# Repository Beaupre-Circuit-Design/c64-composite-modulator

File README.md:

# c64-rf-modulator-replacement
C64 Composite/S-Video RF Modulator Replacement

## Quick Links
* [Schematic](pdf/C64-Composite-Modulator.pdf)

* [Gerber Files](./gerbers)

* [PCB Renderings](./images)

* [Photos](./images)

# Introduction 
This is a remix of mbarszcz-pcb's version of a C64 RF Modulator replacement based on the schematics of similar designs like [Zero-X/OMS's Modified Commodore RF Modulator Design](images/zerox-oms-modulator_simple-schematic.png) and [JMP$FCE2's S-Video only design](images/jmp$fce2-schematic.png). This board can be used to replace a damaged or defective RF modulator in your C64, to improve the sharpness of your video output, or as a modern solution to replace the composite/luma/chroma output functionality of the original modulator on new motherboards such as the SixtyClone or Bwack’s KU-14194.

This design has a few goals that set it apart from the others:

1. It is a universal solution that fits and is electrically compatible with both the C64 and C64C without having to change components on the board or run jumper wires for power.

2. It is inexpensive to build with only a single, small PCB and SMD components that can be assemble by most rapid prototyping compagnies (everything included for JLCPCB but can be easilly adapted for any other service.)

3. It provides high quality S-Video (Y/C) output on the standard A/V output of the C64 while maintaining composite video output for compatibility.

4. It provides adjustable luma/chroma output levels to fine-tune the S-video signal. This allows for the best possible compatibility with a wide variety of different board revisions, VIC chips, aging components and monitors. Adjustable levels mean this board can also be used with s-video cables with or without an inline resistor to eliminate “checkerboarding” caused by too high of a chroma level.

# Compatibility
This RF modulator replacement is compatible with motherboard revisions 250407, 250425, 250466, and 250469, and both NTSC and PAL VIC-II chips. I have not tested it, but I believe it should also be compatible with Bwack's KU-14194 board as well since it uses the standard longboard RF modulator. It is not compatible, however, with the early revision 326298-01 boards with the 5 Pin AV Output. This revision uses a different modulator pin layout, and the video signals are not combined in the modulator. They are instead processed with discrete components inside the VIC-II can.

# Gathering the components
Kicad files are available for you to view or modify as you see fit. Gerber and SMT positioning files are available that can be uploaded directly to JLCPCB to make and assemble your own boards. The Bill of Materials (BOM) can be found [here](C64-Composite-Modulator-Bom.xlsx) with example parts from LCSC and Digikey.

I strongly recommend building the entire board, if you choose to do so, there are a few components that can be omitted in different situations to decrease the cost at the expense of features and flexibility.

## Trimmers
The trim pots used to adjust the luma and chroma are the most expensive components in this project. I highly recommend using them, but if you choose, you may ommit the trimmer pots and install 150Ω resistors instead. This won't give you the precision adjustment of the trimmers, but it will be close enough for most configurations. You can experiment with different fixed value resistors between 100-1KΩ if you want to change fixed output levels.

## No Composite Video
I have not seen any improvement in S-video quality by omitting the composite video components, but if you really don’t want composite output, L1, R8, R9, C6 and V1 can be omitted from the build.

## No Audio Output
A1 can be omitted from the build if you do not want an audio output. Audio will still be available thru the standard A/V output of the C64.

## No Voltage Regulator
If you are only ever going to use the RF modulator replacement on a C64C 250469 short board, you don’t need the voltage regulator or the input/output capacitors since 5V is provided directly to the modulator on pin 1. This means you can omit C1, C2, C3, C4, U1 from the build and permanently jump JP3 pin 2 and 3.

# Building the board
If you wish to assemble the board yourself, i greatly recommend having a SMD Stainless Steel stencil made with your PCB order if you're going with hot air or oven reflow. First step is to start with soldering all the SMD components then the throught holes ones. Finish off by removing the flux residue with some cotton swabs or a brush and isopropyl alcohol.

# Installing the board
First, you need to remove the old RF modulator. This can be a bit tricky as the large metal can will suck the heat right out of the iron. I can’t help you much here, but I can only suggest you use a soldering iron with plenty of heat, use a wide tip, to take your time, and don't rip off any traces. The new board can then be installed one of two ways.

I do not recommend soldering it directly to the motherboard, it will make things much more difficult to remove if you want to upgrade to something else in the futur or come back to the stock modulator.

The PCB can be cut at the dotted lines if you plan to install it on a C64C 250469 short board to reduce footprint.

First solder all the pin headers on the underside, use the LB positions for the large boards and SB for the short boards. Then install the females headers on the motherboards. I personally prefer the rounded pins/receptacles headers but square work just fine too. Solder the female signal headers before the support (LB/SB) headers.

# Adjustments

## Configuring the mainboard
If you are using the longboard (Rev 250407, 250425, 240441, 250466), ground is provided by the support headers, so there is no need to change the G.PAL/I.PAL jumper on the motherboard.

## Jumper Settings
JP1 need to be set accordingly to your VIC-II version, use position 1-2 for NMOS (656x) and 2-3 for HMOS-II (856x).

JP2 control the use of the on-board voltage regulator. For long boards (250407, 250425, and 250466), use position 1-2 to enable the on-board regulator and for C64C short boards (250469) use position 2-3 to bypass it since the board already provide 5v. If you're not sure, check the voltage at pin 2 of JP2. If you get 5v, use position 2-3, else 1-2.

## Adjusting the Output Level
If you choose to include adjustable potentiometers in your build, a counter-clockwise adjustment on the luma (Y) and chroma (C) potentiometers will reduce the output level. A clockwise adjustment will increase the output level. My recommendation is to start with both adjustments fully counter-clockwise and increase as necessary. The levels can be set with a scope or simply “by eye” depending on the tools you have available.

An ideal chroma signal should be ~300mV peak-to-peak (mesured at TP3). The adjustment on the board should allow you to adjust it from approximately ~250mV - 1.7V. This range allows you to dial back the output for use with a standard S-video cable or to turn it up to compensate for the cables with the inline 330-1K resistor. Some monitors don't care if the signal is too hot, others will give you an ugly checkered pattern (especially LCDs). If you don't have an oscilloscope to measure the peak-to-peak voltage, start with the chroma pot fully counter-clockwise and increase it until the colors are sufficiently saturated. If you go too far, the image will begin to look “grainy” or have a checkerboard pattern.

Officially, an ideal luma signal should be 1V PP (including the sync pulse, mesured at TP6). Depending on the output of the VIC-II chip you are using, the adjustment on the board should allow you to adjust it from approximately ~575mV-1.5V PP. The original breadbins output a signal around 1.2V PP, while the later C64Cs were closer to an “in-spec” 1V PP. On some monitors though 1V PP can look too look dark (requiring you to turn up the contrast on your monitor). If using a scope, I would adjust it to approximately 1.1V PP. If adjusting by eye, start low and increase the level until the light blue text is reasonably legible against the dark blue background. If the border and text start to look “white” you have gone too far. Another good test on a CRT is white text on a black background. If the white text is blooming, you should back the signal off. The effect will be very similar to having the contrast set too high.

Composite video output remains at a fixed output level regardless of the Y and C adjustment pots.

# A note on use with LCD Monitors and Checkerboarding
If you are still getting checkerboarding even after adjusting the potentiometers, try populating CO1 with a 330pF Resistor (you can experiement with different values to see what works best with your setup). This combines with R3 to create an RC filter that seems to help eliminate this. There seems to be a degree of variablility regarding different A->D conversion cirtuitry used in different brands of LCD monitors and in devices like the RetroTink2X or OSSC that makes some displays more susceptable to checkerboarding. CRT monitors are not as susceptable to this behavior.

# Changelog
* Rev 20210528-2008
  * Prototype
* Rev 20210531-2143 (Not working)
  * Move B1/B2 silkscreen reference to the right location.
  * Rotate JP1/JP2 so all the headers are aligned to the same side (Forgot to update the silkscreen)
  * Switch to a BC847 transistor but forgot to update the footprint.
* Rev 20220130-1040
  * Corrected aligment of the support headers.
  * Corrected wrong pinout on Q1/Q2.
  * Remove the dual-sid option, not really useful.
  * Change A1 to a RCA Phono jack.
  * Remove B1/B2, use the trimmer pot pads instead if replacing them with a fixed resistor value.
  * Change the footprint of the LCD FIX capacitor for a throught-hole.
  * PCB Layout rework.
  * Fully assembled and tested on both C64 and C64C motherboards.

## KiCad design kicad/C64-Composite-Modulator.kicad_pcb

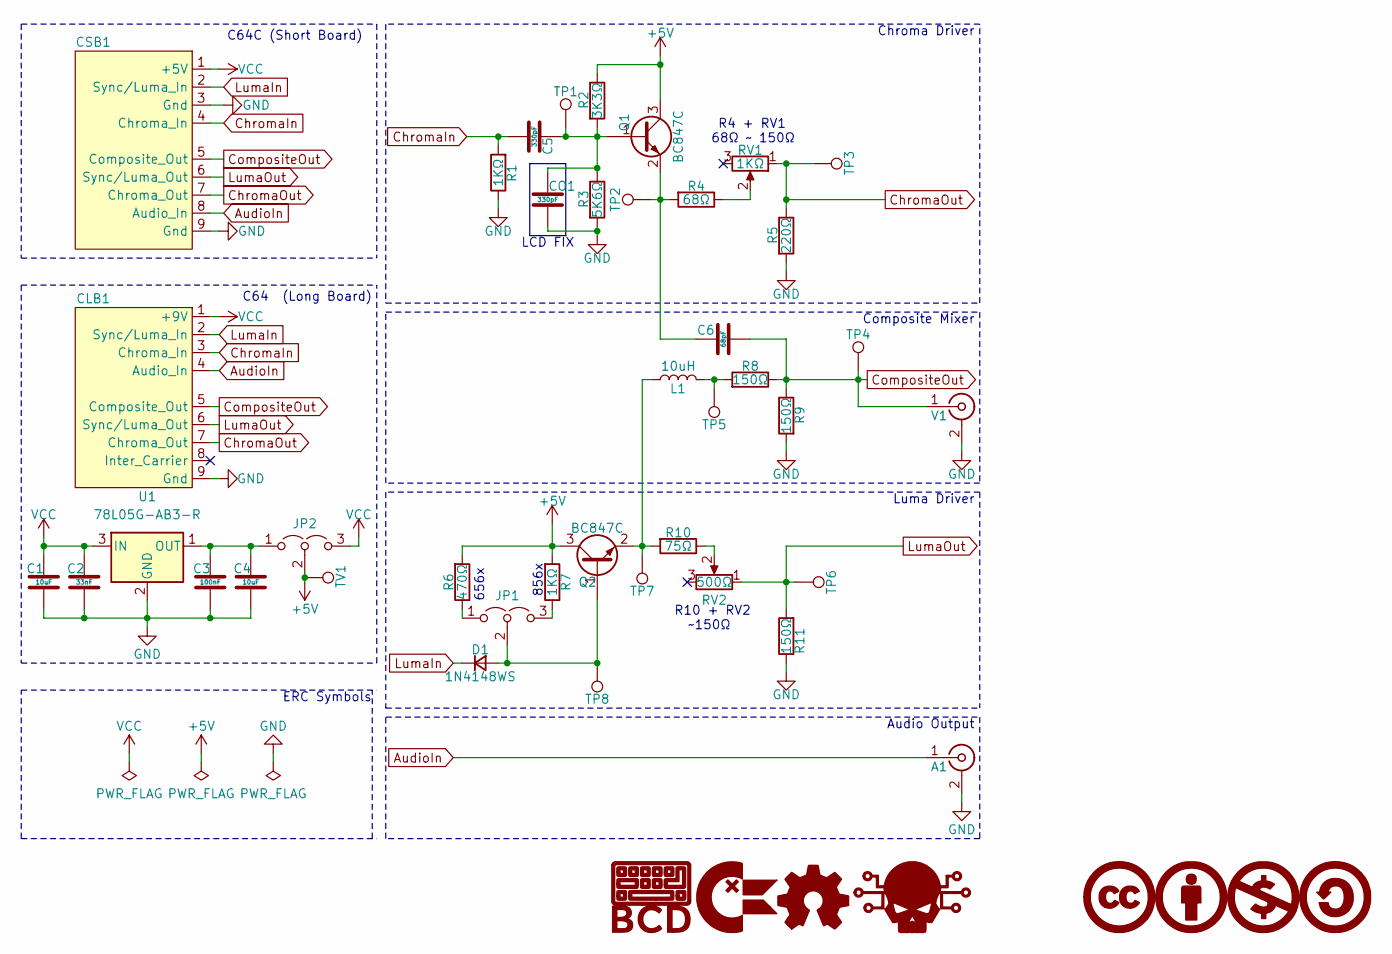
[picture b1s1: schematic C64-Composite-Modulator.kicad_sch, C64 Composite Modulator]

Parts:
A1: Conn_Coaxial; RCJ-013; Mfr.Part RCJ-014; Digikey CP-1403-ND
C1, C4: 10uF; C_1206_3216Metric; Mfr.Part CL31A106KBHNNNE; LCSC C13585
C2: 33nF; C_0805_2012Metric; Mfr.Part 0805B333K500NT; LCSC C1739
C3: 100nF; C_0805_2012Metric; Mfr.Part CL21B104KCFNNNE; LCSC C28233
C5: 330pF; C_0805_2012Metric; Mfr.Part CL21B331KBANNNC; LCSC C51207
C6: 68pF; C_0805_2012Metric; Mfr.Part CL21C680JBANNNC; LCSC C193697
CLB1: Modulator_Board_To_Long_Board; Modulator to Long-Board support; Mfr.Part C49257; Digikey 1212-1172-ND
CO1: 330pF; C_Disc_D4.7mm_W2.5mm_P5.00mm; Mfr.Part CK45-B3AD331KYVNA; LCSC C342340
CSB1: Modulator_Board_To_Short_Board; Modulator to Short-Board support; Mfr.Part C49257; Digikey 1212-1172-ND
D1: 1N4148WS; D_SOD-323F; Mfr.Part 1N4148WS; LCSC C2128
G1: BCD_Logo; BCD_Logo_5mm
G2: ChickenLips; ChickenLips_2.5mm
G3: OpenSource_Hardware; Open_Source_Hardware_2.5mm
G4: Skull; Skull_2.5mm
G5: CreativeCommons; CreativeCommons_2.5mm
G6: CreativeCommons_Attribution; CreativeCommons_Attribution_2.5mm
G7: CreativeCommons_NonCommercial; CreativeCommons_NonCommercial_2.5mm
G8: CreativeCommons_ShareAlike; CreativeCommons_ShareAlike_2.5mm
JP1, JP2: Jumper_3_Open; PinHeader_1x03_P2.54mm_Vertical; Mfr.Part C49257; LCSC C49257
L1: 10uH; L_0805_2012Metric; Mfr.Part SDFL2012S100KTF; LCSC C1046
Q1, Q2: BC847C; SOT-23; Mfr.Part BC847C,215; LCSC C8664
R1, R7: 1KΩ; R_0805_2012Metric; Mfr.Part 0805W8F1001T5E; LCSC C17513
R2: 3K3Ω; R_0805_2012Metric; Mfr.Part 0805W8F3301T5E; LCSC C26010
R3: 5K6Ω; R_0805_2012Metric; Mfr.Part 0805W8F5601T5E; LCSC C4382
R4: 68Ω; R_0805_2012Metric; Mfr.Part 0805W8F680JT5E; LCSC C17802
R5: 220Ω; R_0805_2012Metric; Mfr.Part 0805W8F2200T5E; LCSC C17557
R6: 470Ω; R_0805_2012Metric; Mfr.Part 0805W8F4700T5E; LCSC C17710
R8, R9, R11: 150Ω; R_0805_2012Metric; Mfr.Part 0805W8F1500T5E; LCSC C17471
R10: 75Ω; R_0805_2012Metric; Mfr.Part 0805W8F750JT5E; LCSC C17820
RV1: 1KΩ; Potentiometer_Bourns_3296W_Vertical; Mfr.Part 3296W-1-102; LCSC C118949
RV2: 500Ω; Potentiometer_Bourns_3296W_Vertical; Mfr.Part 3296W-1-500; LCSC C118908
TP1, TP2, TP3, TP4, TP5, TP6, TP7, TP8: TestPoint; TestPoint_THTPad_2.0x2.0mm_Drill1.0mm
TV1: TestPoint; TestPoint_THTPad_2.0x2.0mm_Drill1.0mm
U1: 78L05G-AB3-R; SOT-89-3; Mfr.Part 78L05G-AB3-R; LCSC C71136
V1: Conn_Coaxial; RCJ-014; Mfr.Part RCJ-014; Digikey CP-1403-ND

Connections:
+5V: JP2.2 (C), Q1.3 (C), Q2.3 (C), R2.1, R6.2, R7.2, TV1.1
AudioIn: A1.1 (In), CLB1.4 (Audio_In), CSB1.8 (Audio_In)
ChromaIn: C5.2, CLB1.3 (Chroma_In), CSB1.4 (Chroma_In), R1.2
ChromaOut: CLB1.7 (Chroma_Out), CSB1.7 (Chroma_Out), R5.1, RV1.1, TP3.1
CompositeOut: C6.1, CLB1.5 (Composite_Out), CSB1.5 (Composite_Out), R8.1, R9.1, TP4.1, V1.1 (In)
GND: A1.2 (Ext), C1.2, C2.2, C3.2, C4.2, CLB1.9 (Gnd), CO1.2, CSB1.3 (Gnd), CSB1.9 (Gnd), R1.1, R3.2, R5.2, R9.2, R11.1, U1.2 (GND), V1.2 (Ext)
LumaIn: CLB1.2 (Sync/Luma_In), CSB1.2 (Sync/Luma_In), D1.1 (K)
LumaOut: CLB1.6 (Sync/Luma_Out), CSB1.6 (Sync/Luma_Out), R11.2, RV2.1, TP6.1
unnamed: C3.1, C4.1, JP2.1 (A), U1.1 (OUT)
unnamed: C5.1, CO1.1, Q1.1 (B), R2.2, R3.1, TP1.1
unnamed: C6.2, Q1.2 (E), R4.2, TP2.1
unnamed: D1.2 (A), JP1.2 (C), Q2.1 (B), TP8.1
unnamed: JP1.1 (A), R6.1
unnamed: JP1.3 (B), R7.1
unnamed: L1.1, R8.2, TP5.1
unnamed: L1.2, Q2.2 (E), R10.2, TP7.1
unnamed: R4.1, RV1.2
unnamed: R10.1, RV2.2
VCC: C1.1, C2.1, CLB1.1 (+9V), CSB1.1 (+5V), JP2.3 (B), U1.3 (IN)

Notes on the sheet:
856x
R10 + RV2 ~150Ω
C64C (Short Board)
Luma Driver
Composite Mixer
C64 (Long Board)
ERC Symbols
Audio Output
R4 + RV1 68Ω ~ 150Ω
Chroma Driver
656x
LCD FIX

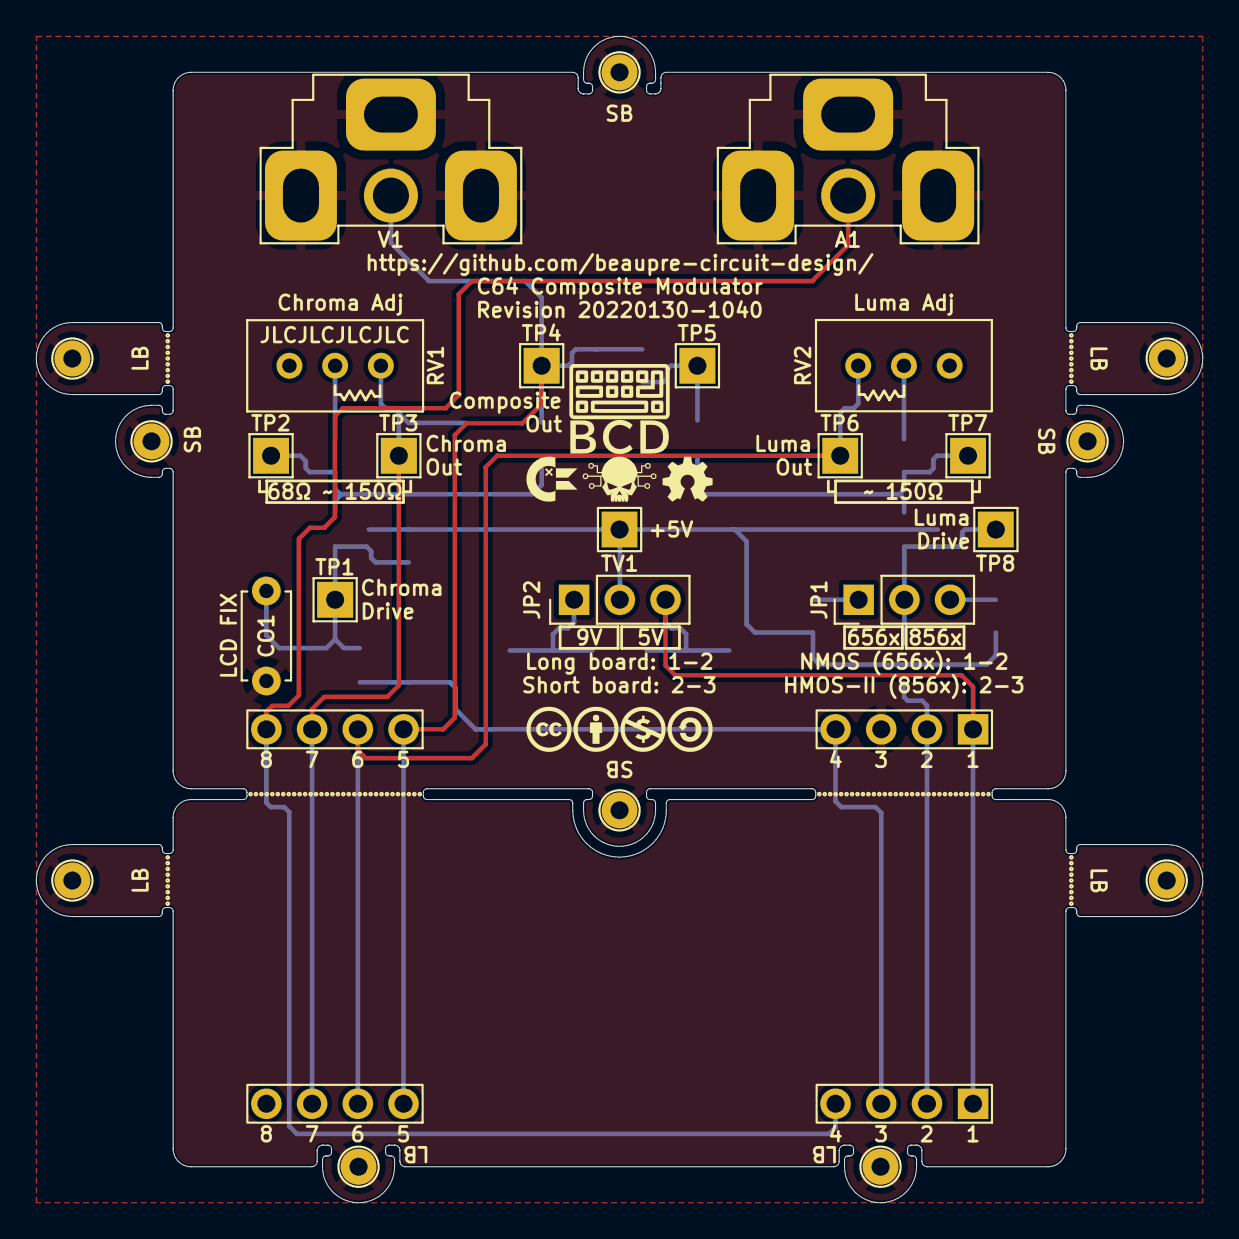
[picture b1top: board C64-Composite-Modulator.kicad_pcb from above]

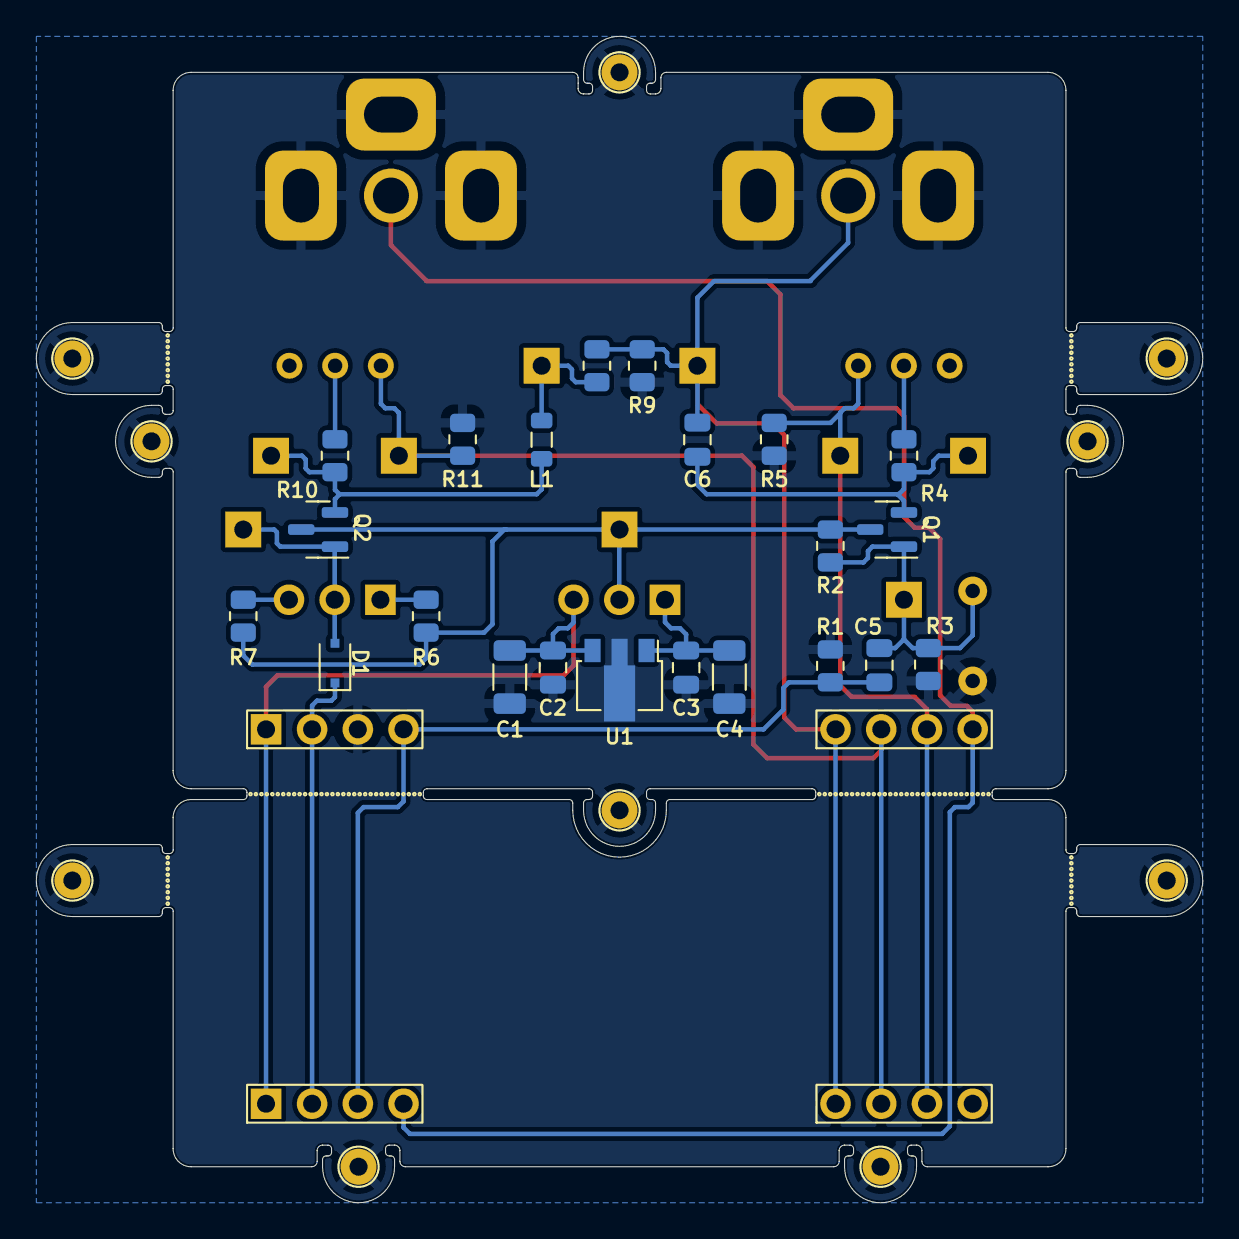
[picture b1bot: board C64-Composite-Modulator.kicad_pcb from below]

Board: 2 copper layers, 64.8 x 64.8 mm, 48 parts (22 on the bottom side), 19 nets.

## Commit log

2021-05-28 Rev 20210528-2008 - Prototype
2021-06-01 Rev 20210531-2143 - Bug Fix
2021-06-01 Cleanup
2022-01-30 Revision 20220130-1040
2022-01-31 Reduce the number of JLCPCB's extended parts
2022-03-24 Updated images and release notes
2022-03-24 Wrong image
